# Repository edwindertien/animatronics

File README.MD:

# Animatronics
## intro
In this archive you will find RPI pico based projects for remote control of animatronics and theatre. 

## designs
Currently there are three physical designs:

- the [MegaAnimaltroniek](/MegaAnimaltroniek/) board is used to controls the bell's and whistles on the animaltroniek machines. Effectively it uses a design developed earlier as 'main' control board. For the animalLove robot it is equipped with a 433Mhz RF link at 9600 bd instead of the (standard) RS485 (57600 bd) over UTP cable. These settings (per vehicle) are placed in the config.h file
- the [picoControl](/picoControl) module which is designed to interface with different radio modules, links to RS485/dynamixel, has two sound modules and expansion ports for Relays and / or Servos (using PCF9685) or PCF9635 (pin compatible) for Relais only. Currently in version 2 (V2.0) and the main PCB in new machines, including LUMI, Animaltroniek, animalLove and more. The version 3.0/3.5 are compact and lacking the 9685/9635 drivers. Currently the sources are optimised for using (bidirectional) ELRS, the other (nrf24L01 / APC220) radio links have been neglected for a while. 
- the [picoRemote](/picoRemote) contains a 4067 mux to allow 16 analog channels (joysticks, buttons, poteniometers), OLED display and radio module of choice. Currently in version 2 (V2.0) and the main source for all remotes. Typically using ELRS 2.4Ghz transmitter, but APC220 can be used as fallback. Also pinout for NRF24L01 is available (but, like with the picoControl, currently not implemented)
- the [picoServo](/picoServo) node, a very small board with RS485, -just- three input and three output ports, power supply and grove I2C socket. This module has been used in the head (as Servo controller) of 'Klara'
- the [picoST3215led](/picoST3215led) node has the same size as the [picoServo](/picoServo) node. It implements the ST3215 (waveshare) servo protocol to control an LED panel (37 neopixel) as Light element in the animatronic Desklight. A more elaborate testing tool for using the ST3215 is implemented using the [st3215andDXLservoMIDI](https://github.com/edwindertien/st3215andDXLservoMIDI)
project. 
## setting up
The development environment consists of VS Code with PlatformIO. Further libraries are installed through the the platformIO library manager (or automagically through the interpretation in

The BetaFPV transmitter and receivers used require the [ExpressLRS configurator](https://www.expresslrs.org/quick-start/installing-configurator/) to be available. Typically the modules are flashed (updated) using the available WIFI method. Currently all modules use (or have been upgraded to) version 4.0.0

## actuators
A large number of different actuators have been used in the system, most of them are currently included in the picoControl module
### waveshare 3215 servo
This servo is used in the desklight arm

### waveshare D210s wheel
This wheel is currently not yet used, 

### generic H-Bridges for DC and BLDC
Most of the H-bridges can be controlled with a number (usually 3 or 4) signals. Typically they include two bits for direction/braking/coasting, a PWM bit and occasionally a separate brake relay. 

Bridges that have been used / tested are:
- pololu [High Ppower Motor Driver 36v20 CS](https://www.pololu.com/product/1457) used for Alan, Helper
- electromen [EM-243C](https://electromen.com/en/motor-controllers/dc-motor-controllers-over-a/em-c-dc-motor-controller-1) - configured with [EM-236A](https://electromen.com/en/supportive-products/electronics/em-a-interface-unit) tool, used for Animaltroniek and AnimalLove.
- electromen [EM-206 BLDC motor](https://electromen.com/en/motor-controllers/brushless-dc-motor-controllers/em-brushless-controller) used for Ravi
- DFRobot 0601 [Dual Channel DC Motor Driver 12A](https://wiki.dfrobot.com/Dual_Channel_DC_Motor_Driver_12A_SKU_DFR0601) to be used for the vacuum cleaner .. 

### cubemars AK60
This is a complex motor unit requiring can-bus. The motor is using a [MCP2515](https://www.tinytronics.nl/en/communication-and-signals/serial/can-bus/mcp2515-can-bus-transceiver-module) module on pins 16,18 and 19, with CS on 17 for SPI0 or 10 (SCK) 11 (MOSI) 12 (MISO) for SPI1 (currently used on the V1.0 board). note that the MCP2515 needs 3.3V but the signal driver 5.0V on a non-joyit module this means cutting the supply line and adding a wire for 5V. 

Configuration software is necessary, but only available for Windows (so a separate tiny windows computer has been acquired to run just the config tool) An FTDI-USB-serial 3.3V edition cable is used to connect the AK60 to the windows PC. Using this tool a motor Address has been set (104) and communication mode. 

### Dynamixel X430 series
like the 'old' MX-64, MX-28 and others, this protocol (dynamixel) is included through the official Robotis library through github (in the platformio.ino: `robotis-git/Dynamixel2Arduino@^0.8.1`)

## SETUPS
### Desklight

Desklight uses picocontrol3 and picoservo2. For the lamp head a 37 hex neopixel pcb is used, which is programmed using these [sources](/../PicoST3215LED/). 

The lamp consists of a [waveshare arm](https://www.waveshare.com/wiki/RoArm-M2-S). The origignal servo configuration is kept, however, one new servo with ID 16 is added to the top, so upon first use the code is executed
```cpp
int ID_ChangeFrom = 1;
int ID_Changeto   = 16;
st.unLockEprom(ID_ChangeFrom);//unlock EPROM-SAFE
st.writeByte(ID_ChangeFrom, SMS_STS_ID, ID_Changeto);//ID
st.LockEprom(ID_Changeto);//EPROM-SAFE locked
```
I'm not sure if data feedback is actually possible with the current hardware implementation, it looks like the 74AC125 is not switching back fast enough for datafeedback. In the current edition the timeout at transmitter side has been reduced, so the control unit does not wait for feedback/update. The bus servo adapter (A) V1.1 by waveshare however does work with datafeeddback from the servos, however, the self-built head light driver does not work with that.  

### Washingmachine (still 'Experimental')

### AMI

//etc

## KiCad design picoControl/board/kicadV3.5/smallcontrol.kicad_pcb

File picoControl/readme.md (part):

# picoControl — Animatronic Robot Control Firmware

RP2040-based receiver firmware for controlling animatronic vehicles via ELRS/CRSF radio.
Built with PlatformIO + EarlPhilhower Arduino core.

---

## Building

```bash
pio run -e animaltroniek_vis    # build one vehicle
pio run                         # build all vehicles (catches regressions)
pio run -e animaltroniek_vis -t upload
```

### Environments

| Environment | Vehicle | Audio | Notes |
|---|---|---|---|
| `animaltroniek_vis` | Fish | none | RS485 passthrough, recorded animation |
| `animaltroniek_kreeft` | Crab | none | RS485 passthrough, recorded animation |
| `animaltroniek_schildpad` | Turtle | none | RS485 passthrough (empty track) |
| `animal_love` | Animal Love | none | RS485 passthrough + expo animation |
| `scuba` | SCUBA diver | 1 player | Jaws sequence, bubble background |
| `ami` | AMI animatronic car | 2 players | Looking sequence, RS485 eyes |
| `lumi` | LUMI light robot | 2 players | Track + sample audio |
| `washmachine` | Washing machine | none | M5 servos, trommel motor |

---

## Hardware

### Board Versions

#### V1 — PCA9685 (PWM LED driver)
- I2C address: `0x40`
- 16-channel PWM output used as relay driver
- `BOARD_V1` in `config.h` → `USE_9685` in `PicoRelay.h`
- Output polarity: `setPWM(n, 0, 4095)` = HIGH = relay OFF; `setPWM(n, 0, 0)` = LOW = relay ON
- **Limitation:** on power-up all outputs default to LOW, briefly activating all relays. Cannot be prevented in software — happens before the RP2040 starts. This was the primary motivation for the V2 board.
- Library: Adafruit PWM Servo Driver

#### V2 — PCA9635 (LED driver)
- I2C address: `0x70` (default; depends on A0-A5 pin configuration on the board)
- 16-channel **open-drain** output
- `BOARD_V2` in `config.h` → `USE_9635` in `PicoRelay.h`
- Output polarity: `PCA963X_LEDON` (01) = output sinks LOW = relay ON; `PCA963X_LEDOFF` (00) = floating/HIGH = relay OFF
- **Advantage:** power-on default is high-impedance — relays stay off at startup
- Must call `setLedDriverMode()` on all 16 channels after `begin()`, otherwise subsequent writes are silently ignored
- Library: robtillaart/PCA9635 v0.6

#### EXTRA_RELAY — 8 additional GPIO relays
Enabled by `EXTRA_RELAY` in `config.h`. Relay numbers 16-23 map to GPIO pins:

| Relay | GPIO |
|---|---|
| 16 | 18 |
| 17 | 19 |
| 18 | 20 |
| 19 | 21 |
| 20 | 22 |
| 21 | 26 |
| 22 | 27 |
| 23 | 28 |

All GPIO relays are low-active: `LOW` = ON, `HIGH` = OFF. Initialised HIGH at startup.

#### Board Version Selection — Critical Rule
`BOARD_Vx` **must** be defined before `#include "Action.h"` in `config.h`, because `Action.h` includes `PicoRelay.h` which uses `BOARD_Vx` to select the chip. It is set once in an early `#if defined(...)` block at the top of `config.h`. For SCUBA/AMI (which can use either board), there is a dedicated section:

```cpp
#if defined(SCUBA) || defined(AMI)
#define BOARD_V2 (1)   // V2 board (PCA9635)
//#define BOARD_V1 (1) // V1 board (PCA9685)
#endif
```

**Never** define `BOARD_Vx` inside a vehicle's own `#ifdef` block — duplicate defines cause the wrong chip to be selected.

### Audio Players
- **Player 1:** DFRobot DF1201S — SoftwareSerial GP6 (RX) / GP7 (TX)
- **Player 2:** DFRobot DF1201S — SoftwareSerial GP16 (RX) / GP17 (TX)
- Initialised on Core 0 in `platformSetup()` with a 5-attempt timeout (2.5s max per player)
- Play/pause commands queued via `AudioQueue` (mutex-protected ring buffer), drained on Core 0 in `platformLoop()`

### RS485
- Hardware UART1, direction controlled via `RS485_SR` pin
- `RS485WriteBuf()` includes `delayMicroseconds(500)` after each packet as an inter-packet gap
- `BUFFER_PASSTHROUGH 9` vehicles send a 9-byte legacy-format buffer every 20Hz tick

---

## Architecture

### Dual-core split

| Core 0 (20 Hz gate) | Core 1 (free-running) |
|---|---|
| Read `channels[]` from Core 1 | CRSF receive + parse |
| Update Actions and Sequences | Map 0-255 per channel |
| RS485 / motor / servo output | Link stats (RSSI, LQ) |
| OLED display | (nothing else — ever) |
| Animation playback | |
| Audio drain + background | |

**Core 1 runs CRSF and nothing else.** `platformSetup1()` and `platformLoopCore1()` are empty for all vehicles. Audio SoftwareSerial calls must never run on Core 1 — they are blocking and halt CRSF reception.

Cores share data via RP2040 SDK mutexes (`pico/mutex.h`).

### Startup sequence
1. Core 0 `setup()` initialises all hardware including `audioInit()` (blocking, up to 2.5s per player)
2. Core 0 sets `_core0SetupDone = true` at the very end of `setup()`
3. Core 1 `setup1()` spins on `_core0SetupDone`, then starts `crsfCore1Setup()`
4. Both cores enter their loops

### Channel protocol — `include/crsf_channels.h`

All 16 channels arrive as 0-255 (mapped from CRSF 172-1811).
**This file must be identical on transmitter and receiver.**

```
channels[0]  CRSF_CH_AXIS_X1        Primary X axis (127=centre)
channels[1]  CRSF_CH_AXIS_Y1        Primary Y axis
channels[2]  CRSF_CH_AXIS_X2        Secondary X (127 if unused)
channels[3]  CRSF_CH_AXIS_Y2        Secondary Y
channels[4]  CRSF_CH_ARM            0=disarmed, 255=armed
channels[5]  CRSF_CH_ANALOG1        Volume/speed pot (0-255)
channels[6]  CRSF_CH_ANALOG2        Spare analog
channels[7]  CRSF_CH_ANALOG3        Spare analog
channels[8]  CRSF_CH_NUNCHUCK_BTN   0=none, 64=Z, 128=C, 192=both
channels[9]  CRSF_CH_KEYPAD_LO      Keypad bits 0-7
channels[10] CRSF_CH_KEYPAD_HI      Keypad bits 8-11
channels[11] CRSF_CH_SW_MUX_0_3     Switch bank A (mux ch 0-3, 2 bits each)
channels[12] CRSF_CH_SW_MUX_4_7     Switch bank B (mux ch 4-7)
channels[13] CRSF_CH_SW_MUX_8_11    Switch bank C (mux ch 8-11)
channels[14] CRSF_CH_SW_MUX_12_15   Switch bank D (mux ch 12-15)
channels[15] CRSF_CH_SPARE          Always 127
```

Switch state per mux channel: `SWITCH_HIGH(sw,n)` (state==2), `SWITCH_MID(sw,n)` (state==1), `SWITCH_LOW(sw,n)` (state==0).
Keypad: `KEYPAD_PRESSED(lo, hi, KEY_BIT_5)` etc.
Nunchuck: `NUNCHUCK_C(channels)` = C pressed (128), `NUNCHUCK_Z(channels)` = Z pressed (64), `NUNCHUCK_BOTH` = both (192).

---

## Action system

```cpp
Action(SW(n,2), relaynr, mode)                               // mux ch n HIGH -> relay
Action(SW(n,1), relaynr, mode)                               // mux ch n MID -> relay
Action(SW(n,0), relaynr, mode)                               // mux ch n LOW -> relay
Action(KEY_ACTION(KEY_BIT_5), relaynr, mode, ..., track, &player1)  // keypad -> audio
Action(-1, relaynr, TRIGGER)                                 // internal/sequence-driven only
```

**Button encoding:**

| Value | Meaning |
|---|---|
| `SW(n, 2)` = n (0-15) | Mux channel n, state HIGH |
| `SW(n, 1)` = 50+n | Mux channel n, state MID |
| `SW(n, 0)` = 30+n | Mux channel n, state LOW |
| `KEY_ACTION(KEY_BIT_x)` = 100+bit | Keypad key |
| `-1` | Never fires from remote |

**Modes:** `DIRECT` (held), `TOGGLE` (press/press), `TRIGGER` (one-shot, no auto-stop from `update()`)

**Important:** actions driven by sequences must use `button=-1` and `TRIGGER` mode. A `DIRECT` action triggered by a sequence is immediately stopped by `update()` on the next tick because the button is not physically held.

---

## Animation system

### `animationStep` struct (`include/Animation.h`)

9 bytes per step recorded at 20 Hz:

```cpp
typedef struct {
  uint8_t axis_x;       // CRSF_CH_AXIS_X1
  uint8_t axis_y;       // CRSF_CH_AXIS_Y1
  uint8_t nunchuck;     // CRSF_CH_NUNCHUCK_BTN (0/64/128/192)
  uint8_t keypad_lo;    // CRSF_CH_KEYPAD_LO (bits 0-7)
  uint8_t analog1;      // CRSF_CH_ANALOG1 (volume/speed)
  uint8_t sw_mux_0_3;   // CRSF_CH_SW_MUX_0_3
  uint8_t sw_mux_4_7;   // CRSF_CH_SW_MUX_4_7
  uint8_t sw_mux_8_11;  // CRSF_CH_SW_MUX_8_11
  uint8_t sw_mux_12_15; // CRSF_CH_SW_MUX_12_15
} animationStep;
```

Binary layout is identical to the original struct — all existing `Track-xxx.h` files work without modification.

### Embedding actuator commands in a track
Switch bank fields encode 4 mux channels x 2 bits each. To activate mux channel N during playback, add the appropriate value to the relevant field. Example [animal_love]: mux ch 2 MID (`SW(2,1)`) in `sw_mux_0_3` (field 5) = add `16`. This allows actuators (sirens, motors, etc.) to be embedded in recorded tracks without a separate sequence.

### Recording a new animation
1. Uncomment `#define ANIMATION_DEBUG` in `config.h` for your vehicle
2. Flash and open serial monitor
3. Move controls — each 20 Hz tick prints one line:
   `{axis_x,axis_y,nunchuck,keypad_lo,analog1,sw0-3,sw4-7,sw8-11,sw12-15},`
4. Copy output, paste as the array body in `Track-xxx.h`
5. Set `DEFAULT_STEPS` to the number of lines
6. Comment out `ANIMATION_DEBUG`, rebuild

### Animation trigger
`ANIMATION_KEY` in `config.h` is the mux channel number. `ANIMATION_KEY_STATE` (0/1/2, default 2) sets which switch state triggers playback:

```cpp
#define ANIMATION_KEY        12   // mux channel
#define ANIMATION_KEY_STATE   2   // HIGH = SW(12,2)
```

The `ANIMATION_KEY_PRESSED` macro in `main.cpp` resolves to the correct `getRemoteSwitch*()` call. The animation key channel is always updated from live CRSF data during playback so releasing the switch correctly stops the animation.

---

## Debug flags

All flags are commented out by default and compiled away when inactive:

| Flag | Effect |
|---|---|
| `ANIMATION_DEBUG` | Prints channel values at 20 Hz for animation recording |
| `ANIMATION_KEY_DEBUG` | Dumps switch banks and animation key state every 1s |
| `RS485_DEBUG` | Mirrors RS485 TX buffer to serial every 1s |
| `RELAY_DEBUG` | Prints `RELAY ON/OFF: n` on every relay state change |
| `RELAY_TEST` | Enables `t` (flash all relays) and `r` (I2C scan) serial commands |
| `AUDIO_DEBUG` | Prints `AUDIO P1/P2 PLAY/PAUSE track=n` |
| `INPUT_DEBUG` | Prints all switch states, keypad bits, and nunchuck value every 500ms |

---

## Per-vehicle config (`include/config.h`)

Key flags:

| Flag | Effect |
|---|---|
| `USE_AUDIO 1/2` | Enable 1 or 2 DFRobot audio players |
| `USE_MOTOR` | Enable DC motor control |
| `USE_RS485` | Enable RS485 output |
| `BUFFER_PASSTHROUGH 9` | Send 9-byte legacy RS485 buffer each tick |
| `USE_OLED` | Enable 128x32 OLED display |
| `USE_CRSF` | Enable ELRS/CRSF radio (Core 1) |
| `USE_SPEEDSCALING` | Enable nunchuck-based speed scaling for motors |
| `ANIMATION_KEY n` | Mux channel number for animation trigger |
| `ANIMATION_KEY_STATE n` | Switch state (0/1/2) that triggers animation |
| `ANIMATION_TRACK_H` | Track file to include (e.g. `"Track-vis.h"`) |
| `BACKGROUND_TRACK_1` | Track number for auto-restarting background audio on player 1 |
| `EXTRA_RELAY` | Enable 8 additional GPIO relay channels (16-23) |
| `EXPO_KEY` | GPIO pin for expo animation trigger (INPUT_PULLUP) |

---

## CRSF link / RSSI

CRSF runs on Core 1, completely isolated from Core 0.
`core1_crsf.cpp` parses both `0x16` (RC channels) and `0x14` (link statistics) frames.

Link statistics via `crsfGetLinkStats(CrsfLinkStats& out)`:
- `rssi_ant1` — uplink RSSI in dBm (signed, e.g. -64)
- `link_quality` — uplink LQ 0-100%
- `downlink_rssi` / `downlink_lq` — nanoRX to TX module link

On RF loss (>500ms): mode to IDLE, `channels[]` reset to `saveValues`.
Serial: `CRSF: LOST` > `CRSF RESTART #N` (exponential backoff) > `CRSF: ACTIVE (recovered)`.

---

## OLED display (128x32)

```
x=0   Vehicle name (3 chars)   SCU / AMI / LUM / KRE / VIS / SCH / LOV / WAS
x=20  Mode                      "act" or "idle"
x=44  Sequence/platform status  "sq:4s" when animation playing, platformScreen() otherwise
x=86  Link quality              "LQ:100%"

Middle: J1 joystick | nunchuck C/Z dots | J2 joystick | 4x4 switch grid | 3x4 keypad | signal bars + dBm
Bottom: Volume bar
```

---

## RS485 passthrough (animaltroniek / animal_love vehicles)

`BUFFER_PASSTHROUGH 9` — 9 bytes sent every 20Hz:

```
[0] axis_x
[1] axis_y
[2] nunchuck raw (0=none, 64=Z, 128=C, 192=both)
[3] keypad ASCII char (first pressed key, 0=none)
[4] volume (analog1)
[5] sw_mux_0_3
[6] sw_mux_4_7
[7] sw_mux_8_11
[8] sw_mux_12_15
```

During animation playback, values come from the track file rather than live RF.

---

## Adding a new vehicle

1. **`platformio.ini`** — add `[env:myvehicle]` with `-DMYVEHICLE`
2. **`config.h`** — add `#ifdef MYVEHICLE` block. Board version in early block only.
3. **`src/platform_myvehicle.cpp`** — implement the 6 platform functions:

```cpp
void platformSetup();       // Core 0: init, audioInit(), configureSequences()
void platformLoop();        // Core 0: sequences, drainAudioQueue(), RS485
void platformScreen();      // Core 0: text for x=44 on OLED top row
void platformOnIdle();      // Core 0: called when RF link lost
void platformSetup1();      // Core 1: leave empty
void platformLoopCore1();   // Core 1: leave empty
```

---

## Vehicle status

| Vehicle | Status | Notes |
|---|---|---|
| animaltroniek_vis | working | Animation, RS485, switches, nunchuck confirmed |
| animaltroniek_kreeft | compile | Same hardware as vis |
| animaltroniek_schildpad | compile | Empty track |
| animal_love | working | Animation, expo sequence, siren, motors confirmed |
| scuba | working | Jaws sequence, audio, relays, snorkel confirmed |
| ami | working | Looking sequence, audio, 24 relays, RS485 eyes confirmed |
| lumi | compile | Untested with new transmitter |
| washmachine | compile | Untested with new transmitter |

---

## Track visualisation tool

The `tools/` directory contains a Python visualiser for inspecting and verifying animation tracks before flashing.

### Setup

```bash
pip install matplotlib pyyaml
```

### Usage

Run from the project root:

```bash
# View interactively (example for animal_love)
python3 tools/track_visualiser.py src/Track-animalove.h tools/channel_map_animal_love.yaml --animation expo

# Save to PNG (place output in docs/ for documentation)
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
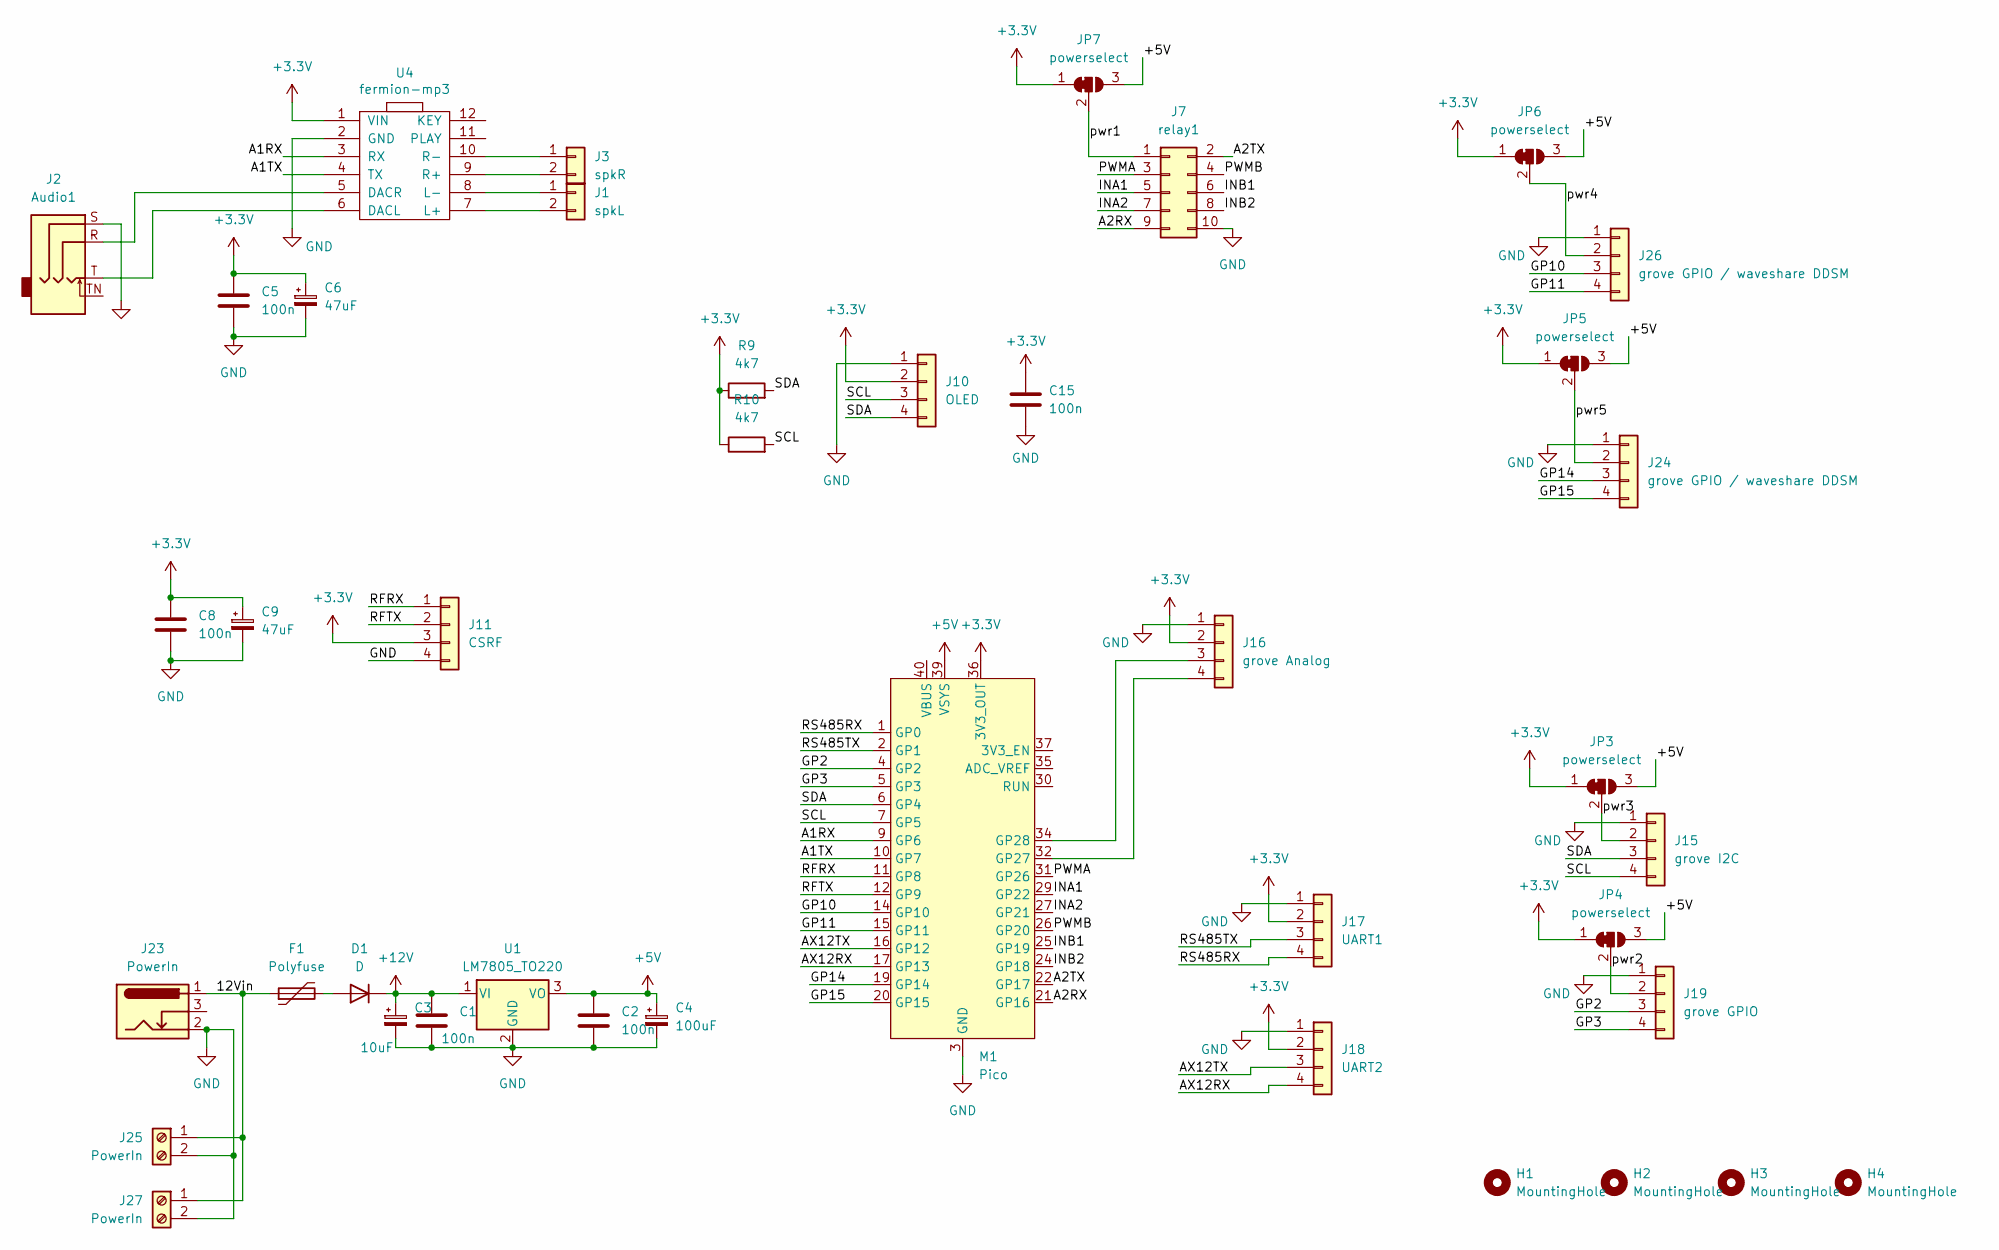
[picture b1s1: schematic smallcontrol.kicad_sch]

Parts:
C1, C2, C5, C8, C15: 100n; C_0603_1608Metric_Pad1.08x0.95mm_HandSolder
C3: 10uF; CP_Elec_4x5.4
C4: 100uF; CP_Elec_D6.3mm_H6.1mm
C6: 47uF; CP_Elec_D6.3mm_H6.1mm
C9: 47uF; CP_Elec_4x5.4
D1: D; D_2114_3652Metric_Pad1.85x3.75mm_HandSolder
F1: Polyfuse; Fuse_1812_4532Metric
H1, H2, H3, H4: MountingHole; MountingHole_3mm
J1: spkL; JST_EH_B2B-EH-A_1x02_P2.50mm_Vertical
J2: Audio1; Jack_3.5mm_CUI_SJ1-3525N_Horizontal
J3: spkR; JST_EH_B2B-EH-A_1x02_P2.50mm_Vertical
J7: relay1; PinHeader_2x05_P2.54mm_Vertical
J10: OLED; OLED128x32
J11: CSRF; PinHeader_1x04_P2.54mm_Vertical
J15: grove I2C; NS-Tech_Grove_1x04_P2mm_Vertical
J16: grove Analog; NS-Tech_Grove_1x04_P2mm_Vertical
J17: UART1; NS-Tech_Grove_1x04_P2mm_Vertical
J18: UART2; NS-Tech_Grove_1x04_P2mm_Vertical
J19: grove GPIO; NS-Tech_Grove_1x04_P2mm_Vertical
J23: PowerIn; BarrelJack_Horizontal
J24, J26: grove GPIO / waveshare DDSM; NS-Tech_Grove_1x04_P2mm_Vertical
J25, J27: PowerIn; TerminalBlock_OnShore_1x02_P3.50mm_Horizontal
JP3, JP4, JP5, JP6, JP7: powerselect; SolderJumper-3_P1.3mm_Bridged2Bar12_RoundedPad1.0x1.5mm
M1: Pico; RaspberryPi_PicoW_SocketTHT
R9, R10: 4k7; R_0603_1608Metric_Pad0.98x0.95mm_HandSolder
U1: LM7805_TO220; TO-220-3_Vertical
U4: fermion-mp3

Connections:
+3.3V: C5.1, C6.1, C8.1, C9.1, C15.1, J10.2, J11.3, J16.2, J17.2, J18.2, JP3.1 (A), JP4.1 (A), JP5.1 (A), JP6.1 (A), JP7.1 (A), M1.36 (3V3_OUT), R9.1, R10.1, U4.1 (VIN)
+5V: C2.1, C4.1, JP3.3 (B), JP4.3 (B), JP5.3 (B), JP6.3 (B), JP7.3 (B), M1.39 (VSYS), U1.3 (VO)
+12V: C1.1, C3.1, D1.1 (K), U1.1 (VI)
/12Vin: F1.1, J23.1, J25.1, J27.1
/A1RX: M1.9 (GP6), U4.3 (RX)
/A1TX: M1.10 (GP7), U4.4 (TX)
/A2RX: J7.9, M1.21 (GP16)
/A2TX: J7.2, M1.22 (GP17)
/AX12RX: J18.4, M1.17 (GP13)
/AX12TX: J18.3, M1.16 (GP12)
/GP2: J19.3, M1.4 (GP2)
/GP3: J19.4, M1.5 (GP3)
/GP10: J26.3, M1.14 (GP10)
/GP11: J26.4, M1.15 (GP11)
/GP14: J24.3, M1.19 (GP14)
/GP15: J24.4, M1.20 (GP15)
/INA1: J7.5, M1.29 (GP22)
/INA2: J7.7, M1.27 (GP21)
/INB1: J7.6, M1.25 (GP19)
/INB2: J7.8, M1.24 (GP18)
/PWMA: J7.3, M1.31 (GP26)
/PWMB: J7.4, M1.26 (GP20)
/RFRX: J11.1, M1.11 (GP8)
/RFTX: J11.2, M1.12 (GP9)
/RS485RX: J17.4, M1.1 (GP0)
/RS485TX: J17.3, M1.2 (GP1)
/SCL: J10.3, J15.4, M1.7 (GP5), R10.2
/SDA: J10.4, J15.3, M1.6 (GP4), R9.2
/pwr1: J7.1, JP7.2 (C)
/pwr2: J19.2, JP4.2 (C)
/pwr3: J15.2, JP3.2 (C)
/pwr4: J26.2, JP6.2 (C)
/pwr5: J24.2, JP5.2 (C)
GND: C1.2, C2.2, C3.2, C4.2, C5.2, C6.2, C8.2, C9.2, C15.2, J2.S, J7.10, J10.1, J11.4, J15.1, J16.1, J17.1, J18.1, J19.1, J23.2, J24.1, J25.2, J26.1, J27.2, M1.3 (GND), M1.8 (GND), M1.13 (GND), M1.18 (GND), M1.23 (GND), M1.28 (GND), M1.33 (GND), M1.38 (GND), U1.2 (GND), U4.2 (GND)
unnamed: D1.2 (A), F1.2
unnamed: J1.1, U4.8 (L-)
unnamed: J1.2, U4.7 (L+)
unnamed: J3.1, U4.10 (R-)
unnamed: J3.2, U4.9 (R+)
unnamed: J16.3, M1.34 (GP28)
unnamed: J16.4, M1.32 (GP27)
unnamed: J2.T, U4.6 (DACL)
unnamed: J2.R, U4.5 (DACR)

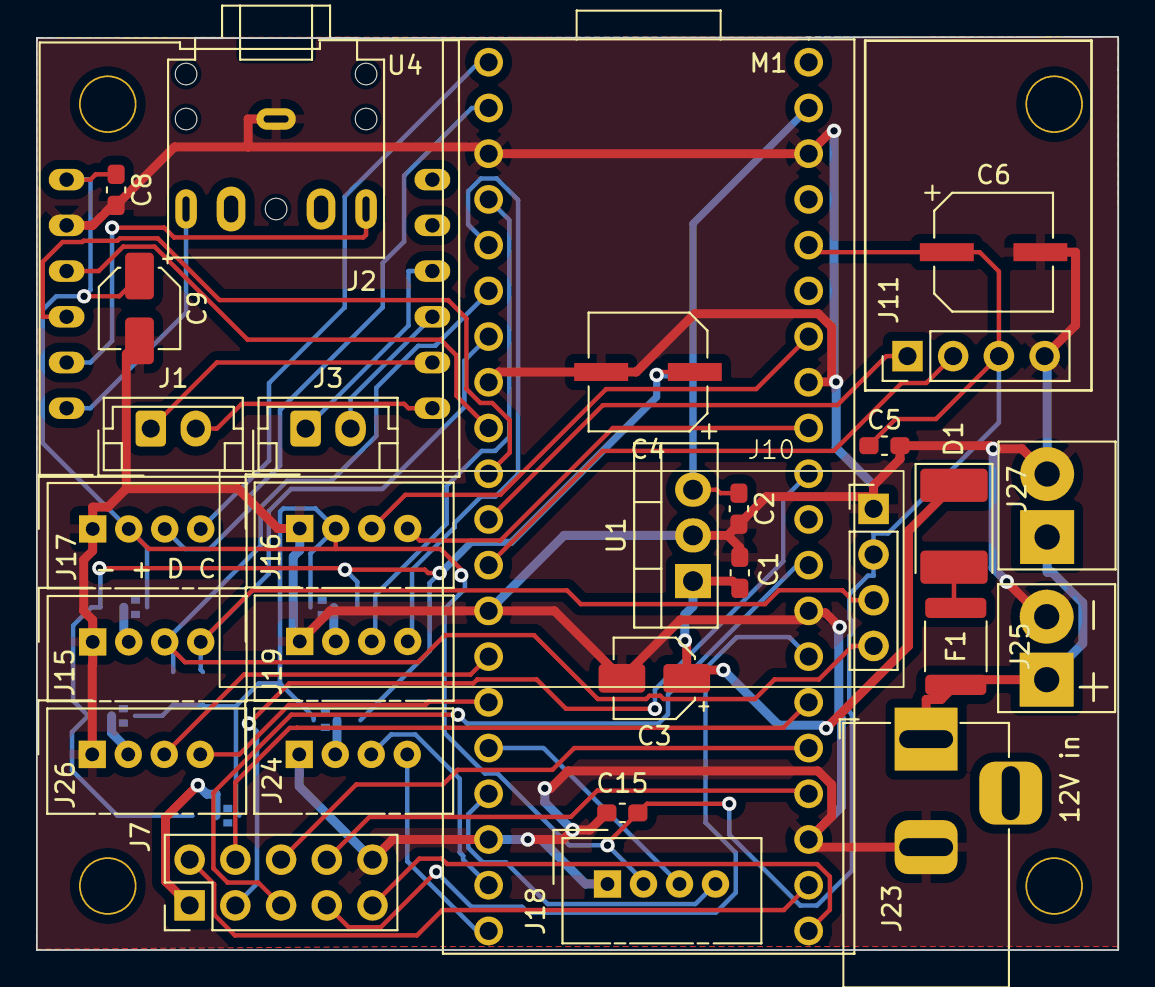
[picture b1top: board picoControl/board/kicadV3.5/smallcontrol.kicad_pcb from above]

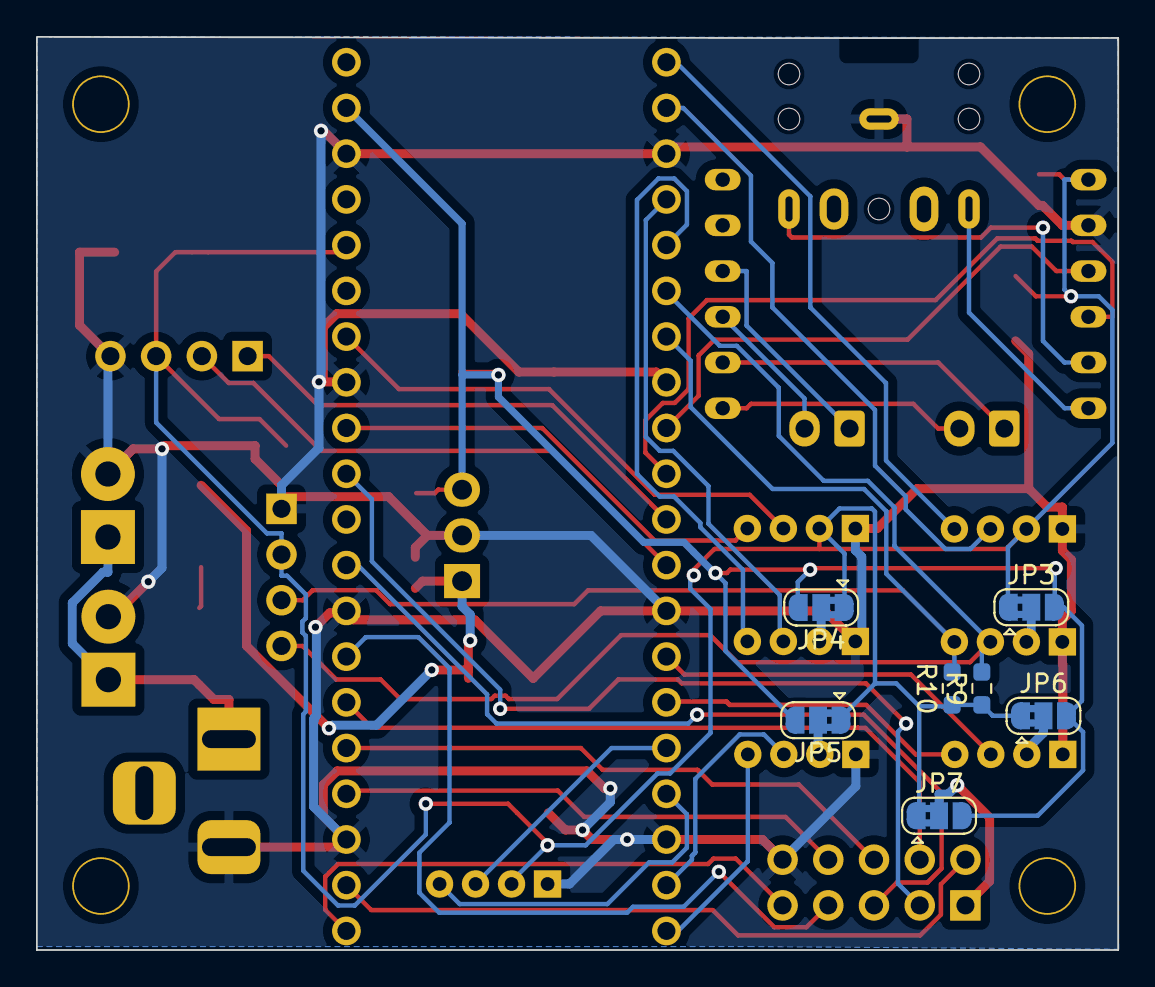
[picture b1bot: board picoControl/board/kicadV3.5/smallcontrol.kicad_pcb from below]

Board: 2 copper layers, 60.1 x 50.7 mm, 41 parts (7 on the bottom side), 43 nets.

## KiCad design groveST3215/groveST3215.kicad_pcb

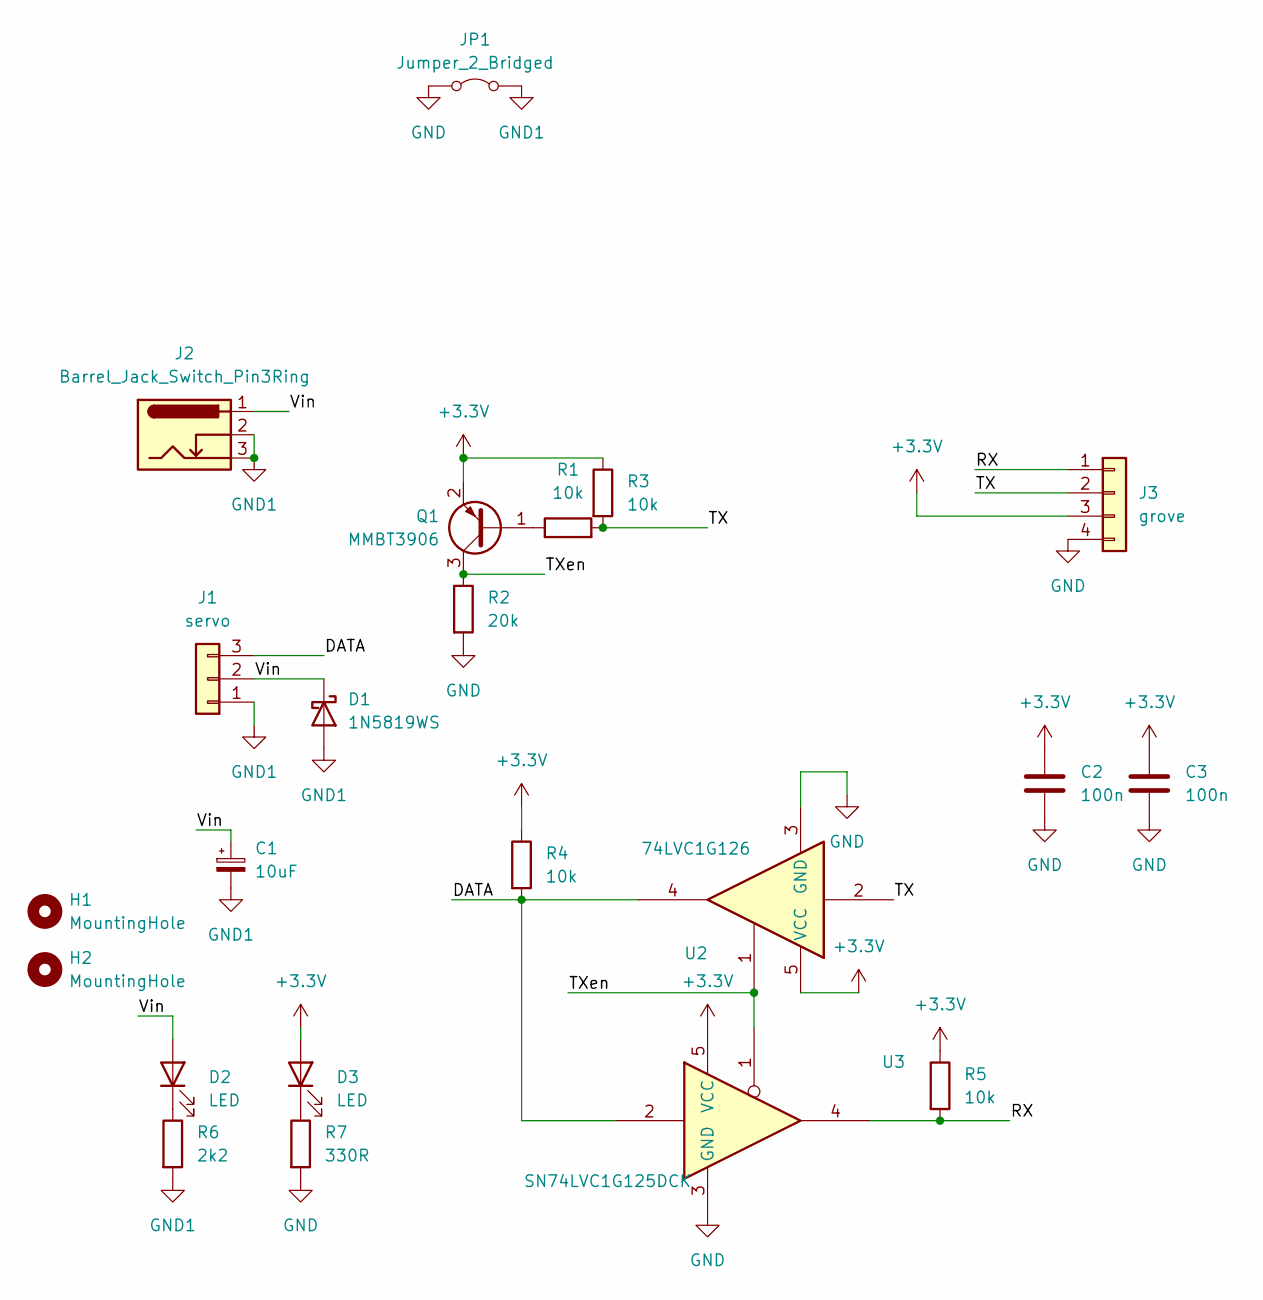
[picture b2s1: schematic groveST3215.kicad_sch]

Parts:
C1: 10uF; CP_Elec_5x4.4
C2, C3: 100n; C_0603_1608Metric_Pad1.08x0.95mm_HandSolder
D1: 1N5819WS; D_SOD-323
D2, D3: LED; LED_0603_1608Metric_Pad1.05x0.95mm_HandSolder
H1, H2: MountingHole; MountingHole_2.2mm_M2_DIN965
J1: servo; Molex_SPOX_5267-03A_1x03_P2.50mm_Vertical
J2: Barrel_Jack_Switch_Pin3Ring; BarrelJack_Horizontal
J3: grove; NS-Tech_Grove_1x04_P2mm_Vertical
JP1: Jumper_2_Bridged; SolderJumper-2_P1.3mm_Bridged_Pad1.0x1.5mm
Q1: MMBT3906; SOT-23
R1, R3, R4, R5: 10k; R_0603_1608Metric_Pad0.98x0.95mm_HandSolder
R2: 20k; R_0603_1608Metric_Pad0.98x0.95mm_HandSolder
R6: 2k2; R_0603_1608Metric_Pad0.98x0.95mm_HandSolder
R7: 330R; R_0603_1608Metric_Pad0.98x0.95mm_HandSolder
U2: 74LVC1G126; SOT-353_SC-70-5_Handsoldering
U3: SN74LVC1G125DCK; SOT-353_SC-70-5_Handsoldering

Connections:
+3.3V: C2.1, C3.1, D3.2 (A), J3.3, Q1.2 (E), R3.1, R4.1, R5.1, U2.5 (VCC), U3.5 (VCC)
/DATA: J1.3, R4.2, U2.4, U3.2
/RX: J3.1, R5.2, U3.4
/TX: J3.2, R1.2, R3.2, U2.2
/TXen: Q1.3 (C), R2.1, U2.1, U3.1
/Vin: C1.1, D1.1 (K), D2.2 (A), J1.2, J2.1
GND: C2.2, C3.2, J3.4, JP1.1 (A), R2.2, R7.2, U2.3 (GND), U3.3 (GND)
GND1: C1.2, D1.2 (A), J1.1, J2.2, J2.3, JP1.2 (B), R6.2
unnamed: D2.1 (K), R6.1
unnamed: D3.1 (K), R7.1
unnamed: Q1.1 (B), R1.1

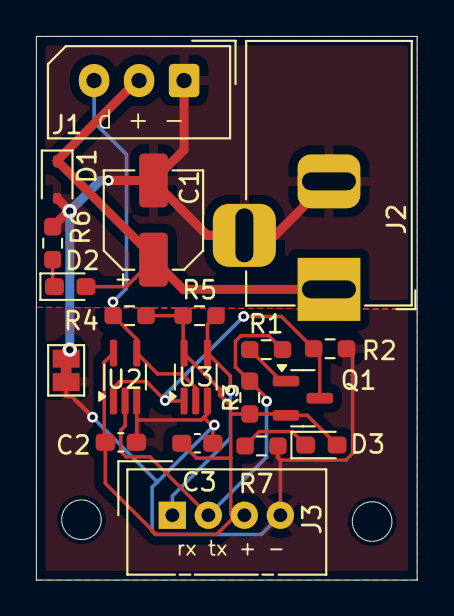
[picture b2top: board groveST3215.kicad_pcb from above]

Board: 2 copper layers, 21.1 x 30.2 mm, 22 parts (0 on the bottom side), 11 nets.

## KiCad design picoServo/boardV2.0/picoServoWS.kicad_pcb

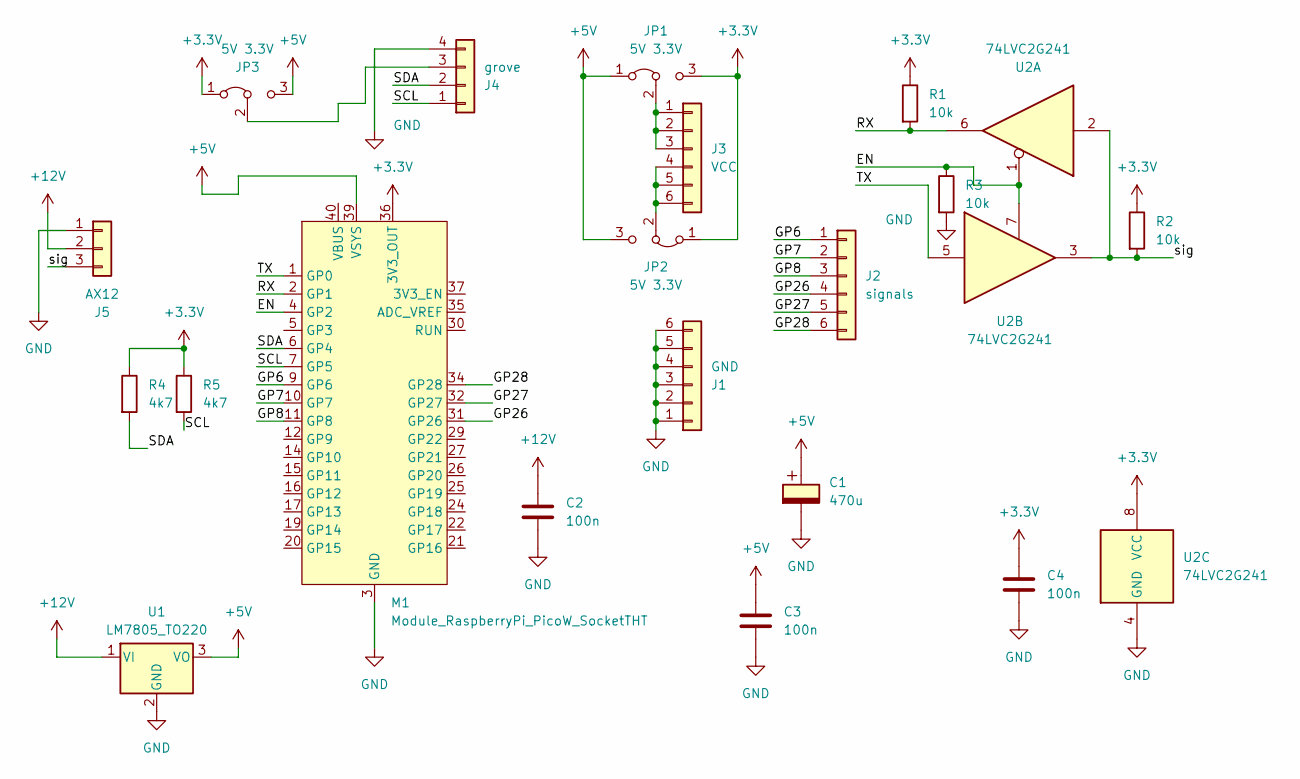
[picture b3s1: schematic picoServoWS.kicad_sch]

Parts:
C1: 470u; CP_Elec_D8.0mm
C2, C3, C4: 100n; C_0603_1608Metric_Pad1.08x0.95mm_HandSolder
J1: GND; PinHeader_1x06_P2.54mm_Horizontal
J2: signals; PinHeader_1x06_P2.54mm_Vertical
J3: VCC; PinHeader_1x06_P2.54mm_Vertical
J4: grove; Molex_Micro-Latch_53253-0470_1x04_P2.00mm_Vertical
J5: AX12; Molex_SPOX_5267-03A_1x03_P2.50mm_Vertical
JP1, JP2, JP3: 5V 3.3V; SolderJumper-3_P1.3mm_Bridged2Bar12_RoundedPad1.0x1.5mm_Num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
M1: Module_RaspberryPi_PicoW_SocketTHT; RaspberryPi_PicoW_SocketTHT
R1, R2, R3: 10k; R_0603_1608Metric_Pad0.98x0.95mm_HandSolder
R4, R5: 4k7; R_0603_1608Metric_Pad0.98x0.95mm_HandSolder
U1: LM7805_TO220; TO-220-3_Vertical
U2: 74LVC2G241; TSSOP-8_3x3mm_P0.65mm

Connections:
+3.3V: C4.1, JP1.3 (B), JP2.1 (A), JP3.1 (A), M1.36 (3V3_OUT), R1.1, R2.1, R4.1, R5.1, U2.8 (VCC)
+5V: C1.1, C3.1, JP1.1 (A), JP2.3 (B), JP3.3 (B), M1.39 (VSYS), U1.3 (VO)
+12V: C2.1, J5.2, U1.1 (VI)
/EN: M1.4 (GP2), R3.1, U2.1, U2.7
/GP6: J2.1, M1.9 (GP6)
/GP7: J2.2, M1.10 (GP7)
/GP8: J2.3, M1.11 (GP8)
/GP26: J2.4, M1.31 (GP26)
/GP27: J2.5, M1.32 (GP27)
/GP28: J2.6, M1.34 (GP28)
/RX: M1.2 (GP1), R1.2, U2.6
/SCL: J4.1, M1.7 (GP5), R5.2
/SDA: J4.2, M1.6 (GP4), R4.2
/TX: M1.1 (GP0), U2.5
/sig: J5.3, R2.2, U2.2, U2.3
GND: C1.2, C2.2, C3.2, C4.2, J1.1, J1.2, J1.3, J1.4, J1.5, J1.6, J4.4, J5.1, M1.3 (GND), M1.8 (GND), M1.13 (GND), M1.18 (GND), M1.23 (GND), M1.28 (GND), M1.33 (GND), M1.38 (GND), R3.2, U1.2 (GND), U2.4 (GND)
unnamed: J3.1, J3.2, J3.3, JP1.2 (C)
unnamed: J3.4, J3.5, J3.6, JP2.2 (C)
unnamed: J4.3, JP3.2 (C)

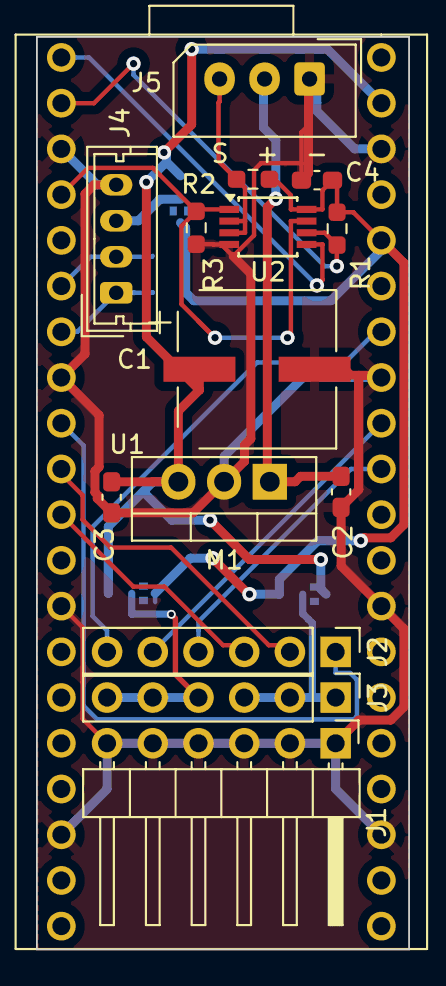
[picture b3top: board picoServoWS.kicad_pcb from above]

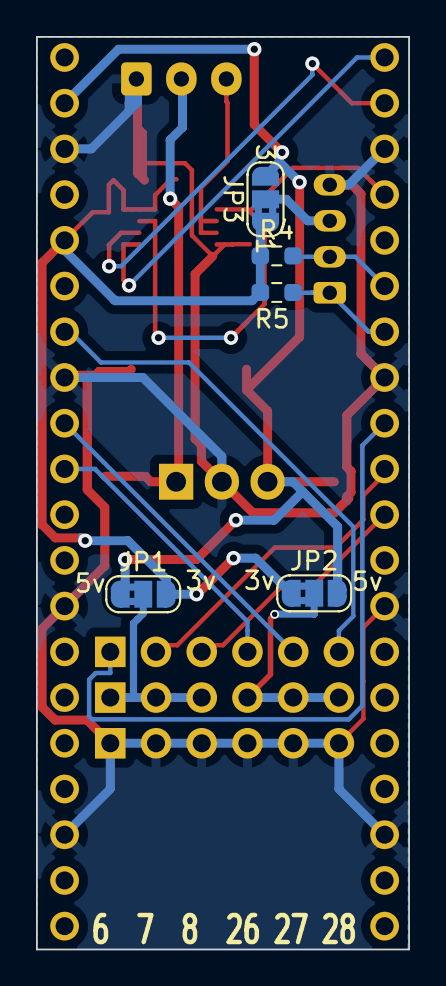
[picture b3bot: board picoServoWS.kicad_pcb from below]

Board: 2 copper layers, 20.7 x 50.7 mm, 20 parts (5 on the bottom side), 19 nets.

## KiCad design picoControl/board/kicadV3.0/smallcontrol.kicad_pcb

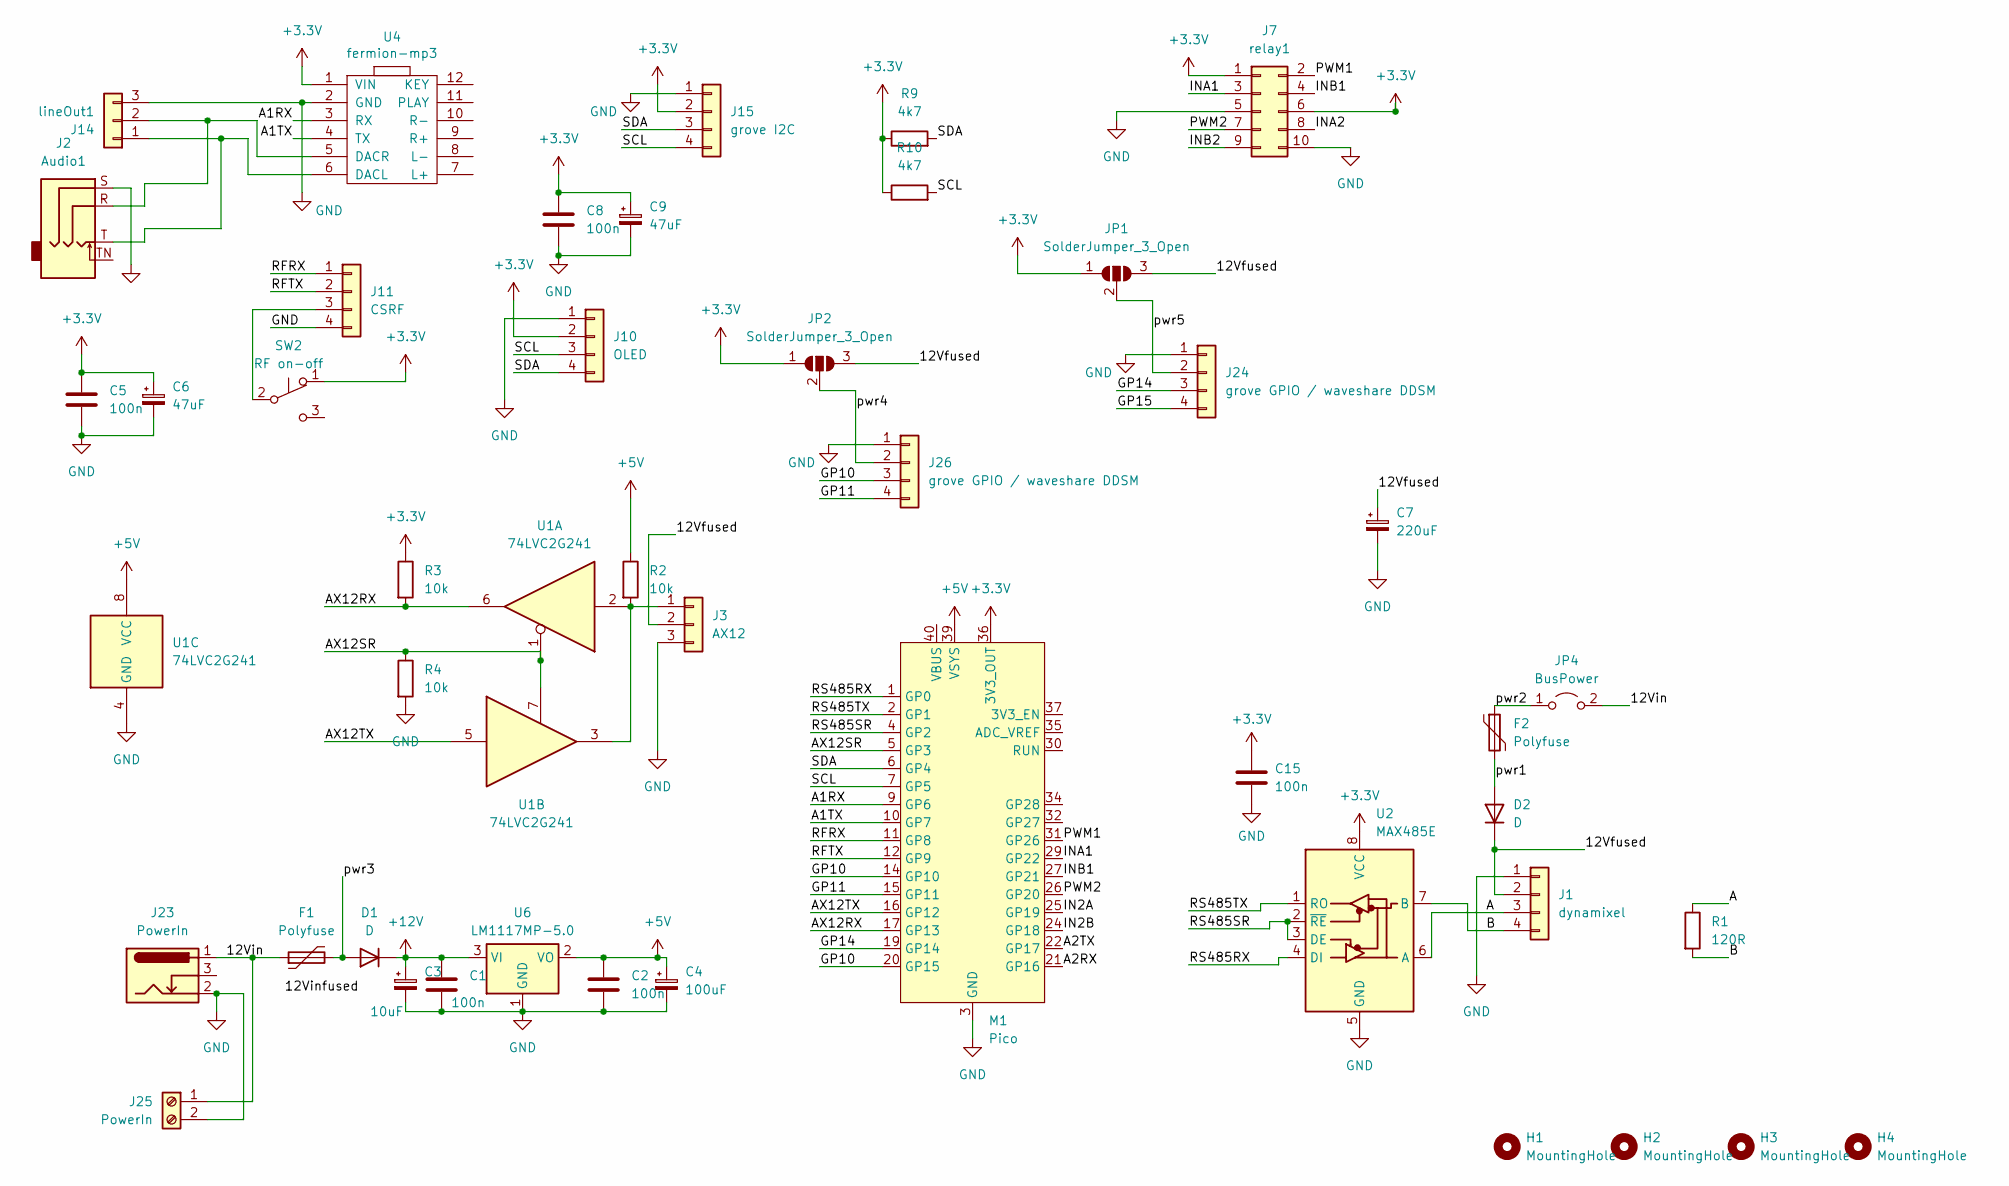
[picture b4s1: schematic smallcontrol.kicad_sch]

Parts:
C1, C2, C5, C8, C15: 100n; C_1206
C3: 10uF; CP_EIA-7132-20_AVX-U_HandSolder
C4: 100uF; CP_EIA-7132-28_AVX-C_HandSolder
C6, C9: 47uF; CP_EIA-7132-20_AVX-U_HandSolder
C7: 220uF; CP_EIA-7132-20_AVX-U_HandSolder
D1, D2: D; D_2114_3652Metric_Pad1.85x3.75mm_HandSolder
F1, F2: Polyfuse; Fuse_1812_4532Metric
H1, H2, H3, H4: MountingHole; MountingHole_3mm
J1: dynamixel; Molex_SPOX_5267-04A_1x04_P2.50mm_Vertical
J2: Audio1; Jack_3.5mm_CUI_SJ1-3525N_Horizontal
J3: AX12; Molex_SPOX_5267-03A_1x03_P2.50mm_Vertical
J7: relay1; PinHeader_2x05_P2.54mm_Vertical
J10: OLED; OLED128x32
J11: CSRF; PinHeader_1x04_P2.54mm_Vertical
J14: lineOut1; PinHeader_1x03_P2.54mm_Vertical
J15: grove I2C; Grove_1x04
J23: PowerIn; BarrelJack_Horizontal
J24, J26: grove GPIO / waveshare DDSM; Grove_1x04
J25: PowerIn; TerminalBlock_OnShore_1x02_P5.00mm_Horizontal
JP1, JP2: SolderJumper_3_Open; SolderJumper-3_P1.3mm_Open_RoundedPad1.0x1.5mm_NumberLabels
JP4: BusPower; PinHeader_1x02_P2.54mm_Vertical
M1: Pico; RaspberryPi_PicoW_SocketTHT
R1: 120R; R_1206
R2, R3, R4: 10k; R_1206
R9, R10: 4k7; R_1206
SW2: RF on-off; SW_Slide-03_Wuerth-WS-SLTV_10x2.5x6.4_P2.54mm
U1: 74LVC2G241; TSSOP-8_3x3mm_P0.65mm
U2: MAX485E; SO-8_3.9x4.9mm_P1.27mm
U4: fermion-mp3
U6: LM1117MP-5.0; SOT-223-3_TabPin2

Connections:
+3.3V: C5.1, C6.1, C8.1, C9.1, C15.1, J7.1, J7.6, J10.2, J15.2, JP1.1 (A), JP2.1 (A), M1.36 (3V3_OUT), R3.1, R9.1, R10.1, SW2.1 (A), U2.8 (VCC), U4.1 (VIN)
+5V: C2.1, C4.1, M1.39 (VSYS), R2.1, U1.8 (VCC), U6.2 (VO)
+12V: C1.1, C3.1, D1.1 (K), U6.3 (VI)
/12Vfused: C7.1, D2.1 (K), J1.2, J3.2, JP1.3 (B), JP2.3 (B)
/12Vin: F1.1, J23.1, J25.1, JP4.2 (B)
/A: J1.3, R1.1, U2.6 (A)
/A1RX: M1.9 (GP6), U4.3 (RX)
/A1TX: M1.10 (GP7), U4.4 (TX)
/A2RX: M1.21 (GP16)
/A2TX: M1.22 (GP17)
/AX12RX: M1.17 (GP13), R3.2, U1.6
/AX12SR: M1.5 (GP3), R4.1, U1.1, U1.7
/AX12TX: M1.16 (GP12), U1.5
/B: J1.4, R1.2, U2.7 (B)
/GP10: J26.3, M1.14 (GP10), M1.20 (GP15)
/GP11: J26.4, M1.15 (GP11)
/GP14: J24.3, M1.19 (GP14)
/GP15: J24.4
/IN2A: M1.25 (GP19)
/IN2B: M1.24 (GP18)
/INA1: J7.3, M1.29 (GP22)
/INA2: J7.8
/INB1: J7.4, M1.27 (GP21)
/INB2: J7.9
/PWM1: J7.2, M1.31 (GP26)
/PWM2: J7.7, M1.26 (GP20)
/RFRX: J11.1, M1.11 (GP8)
/RFTX: J11.2, M1.12 (GP9)
/RS485RX: M1.1 (GP0), U2.4 (DI)
/RS485SR: M1.4 (GP2), U2.2 (~RE), U2.3 (DE)
/RS485TX: M1.2 (GP1), U2.1 (RO)
/SCL: J10.3, J15.4, M1.7 (GP5), R10.2
/SDA: J10.4, J15.3, M1.6 (GP4), R9.2
/pwr1: D2.2 (A), F2.2
/pwr2: F2.1, JP4.1 (A)
/pwr3: D1.2 (A), F1.2
/pwr4: J26.2, JP2.2 (C)
/pwr5: J24.2, JP1.2 (C)
GND: C1.2, C2.2, C3.2, C4.2, C5.2, C6.2, C7.2, C8.2, C9.2, C15.2, J1.1, J2.S, J3.3, J7.5, J7.10, J10.1, J11.4, J14.3, J15.1, J23.2, J24.1, J25.2, J26.1, M1.3 (GND), M1.8 (GND), M1.13 (GND), M1.18 (GND), M1.23 (GND), M1.28 (GND), M1.33 (GND), M1.38 (GND), R4.2, U1.4 (GND), U2.5 (GND), U4.2 (GND), U6.1 (GND)
unnamed: J3.1, R2.2, U1.2, U1.3
unnamed: J11.3, SW2.2 (B)
unnamed: J2.T, J14.1, U4.6 (DACL)
unnamed: J2.R, J14.2, U4.5 (DACR)
